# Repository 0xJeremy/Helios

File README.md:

# Helios Pi Hat Controller

### Board Layout

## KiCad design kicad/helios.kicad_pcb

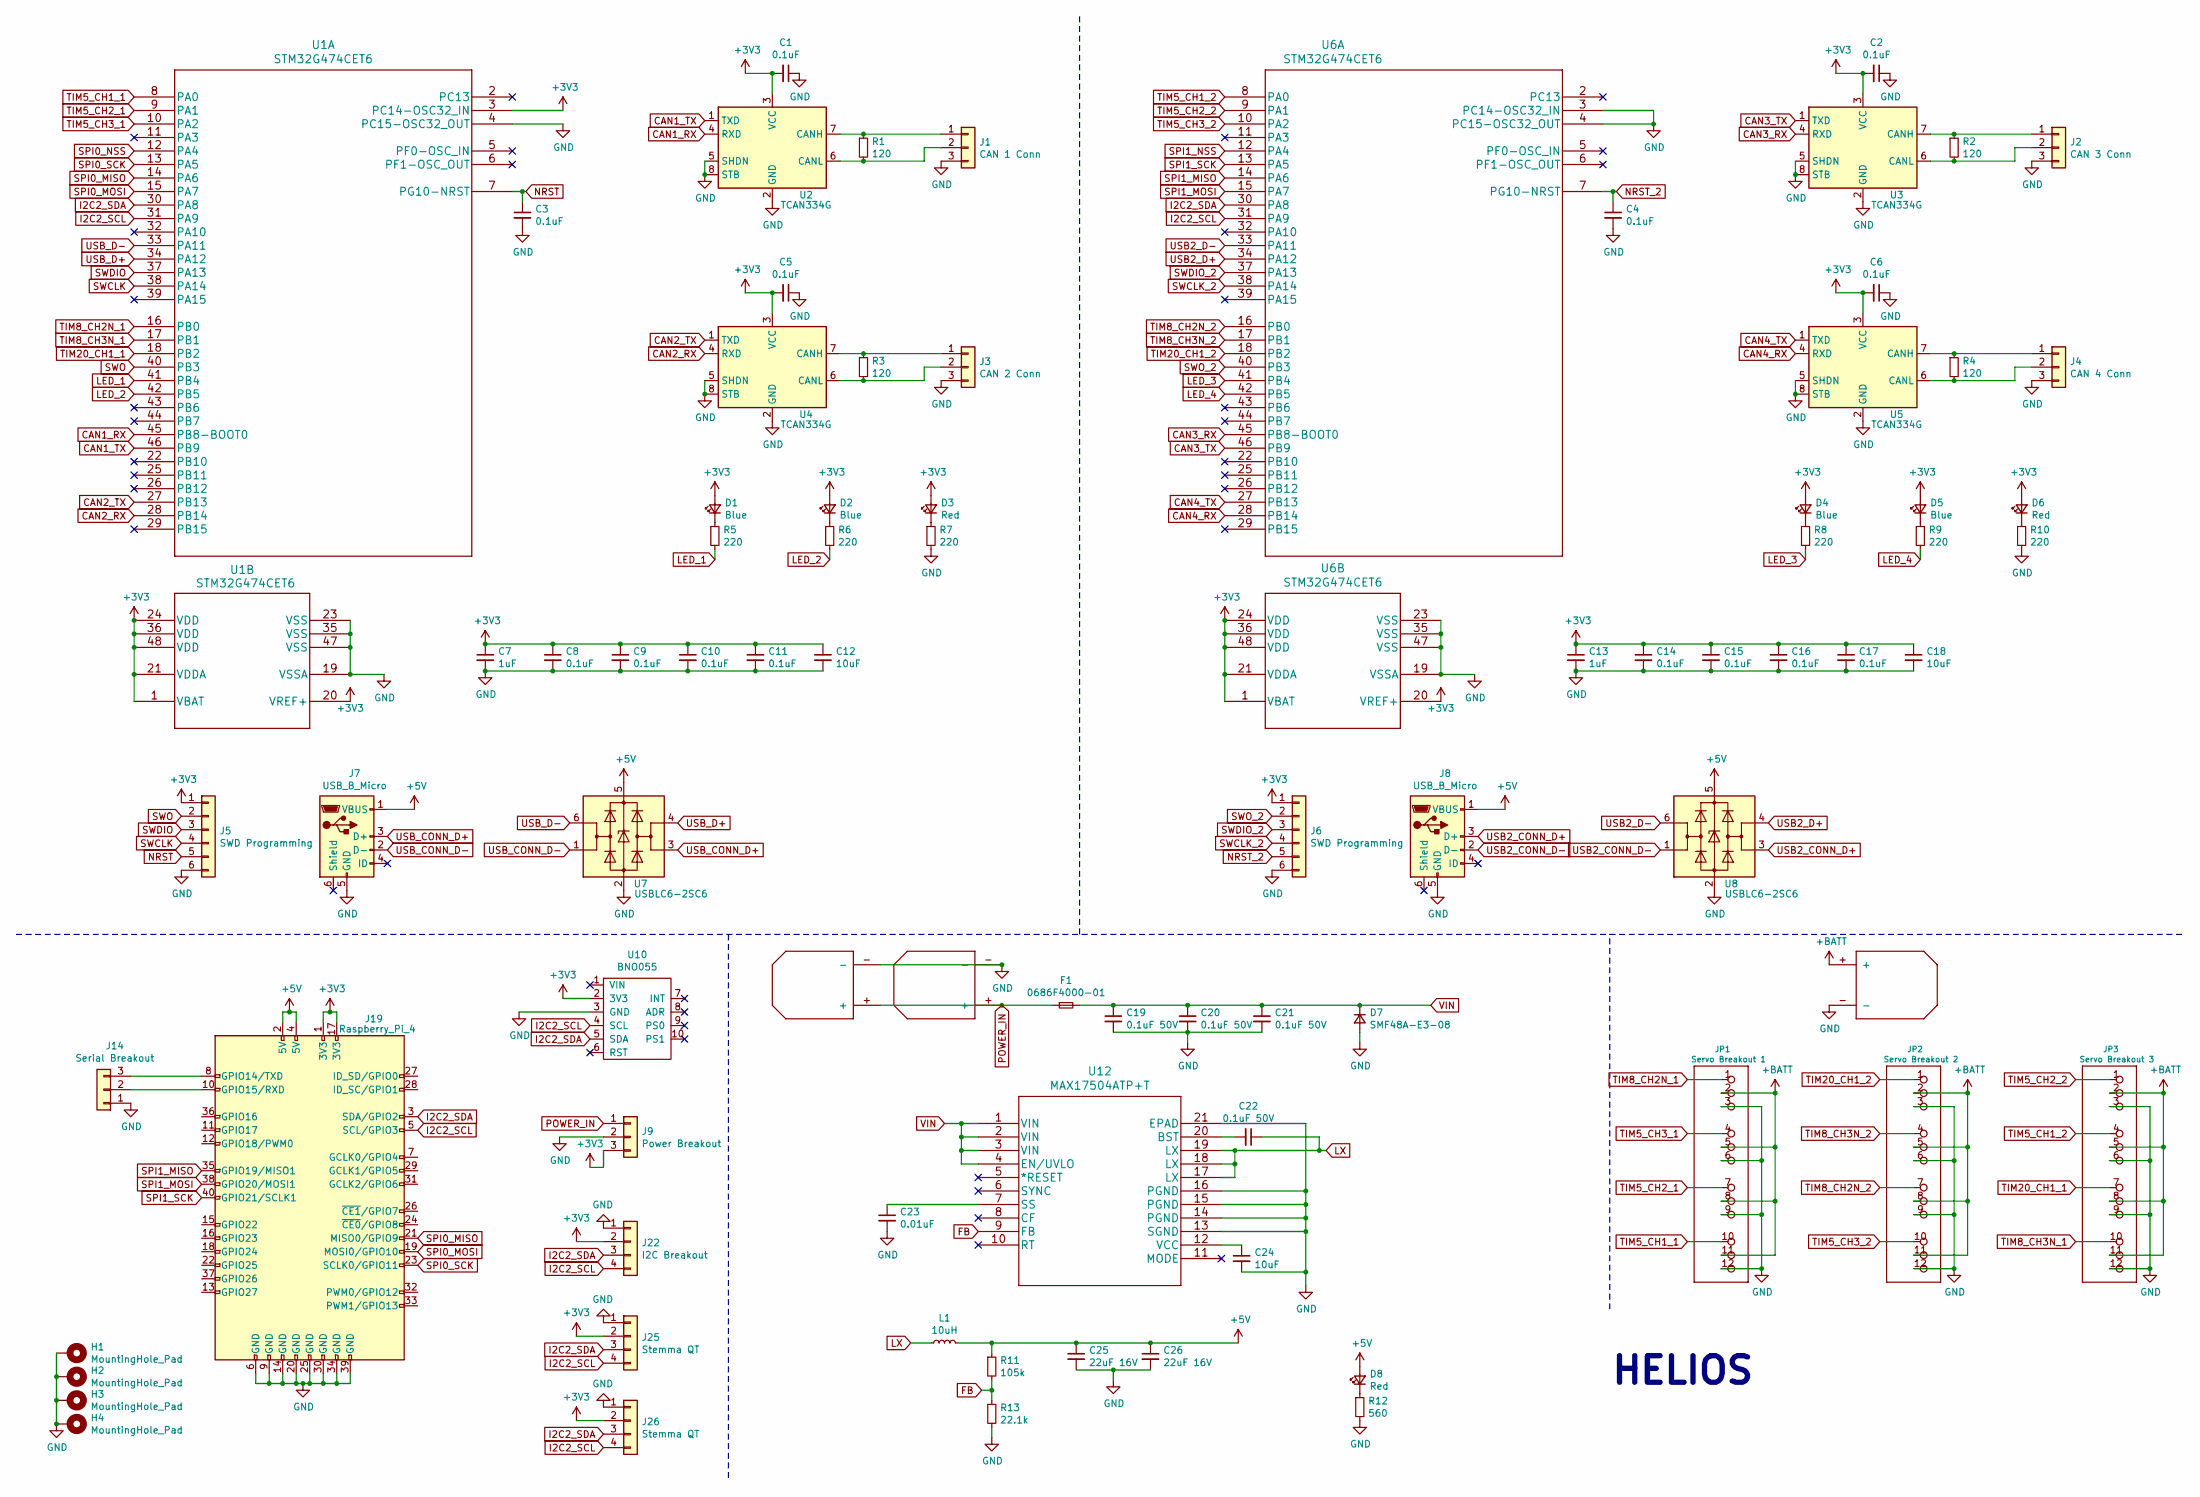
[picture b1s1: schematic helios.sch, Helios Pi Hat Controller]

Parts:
1111: XT30; XT30P
C1, C2, C3, C4, C5, C6, C8, C9, C10, C11, C14, C15, C16, C17: 0.1uF; C_0402_1005Metric
C7, C13: 1uF; C_0402_1005Metric
C12, C18: 10uF; C_0402_1005Metric
C19, C20, C21, C22: 0.1uF 50V; C_1206_3216Metric
C23: 0.01uF; C_0402_1005Metric
C24: 10uF; C_1206_3216Metric
C25, C26: 22uF 16V; C_0603_1608Metric
D1, D2, D4, D5: Blue; LED_0603_1608Metric
D3, D6, D8: Red; LED_0603_1608Metric
D7: SMF48A-E3-08; SMF
F1: 0686F4000-01; Fuse_0603_1608Metric
H1, H2, H3, H4: MountingHole_Pad; MountingHole_2.7mm_M2.5_DIN965_Pad
J1: CAN 1 Conn; JST_PH_B3B-PH-K_1x03_P2.00mm_Vertical
J2: CAN 3 Conn; JST_PH_B3B-PH-K_1x03_P2.00mm_Vertical
J3: CAN 2 Conn; JST_PH_B3B-PH-K_1x03_P2.00mm_Vertical
J4: CAN 4 Conn; JST_PH_B3B-PH-K_1x03_P2.00mm_Vertical
J5, J6: SWD Programming; JST_PH_B6B-PH-K_1x06_P2.00mm_Vertical
J7, J8: USB_B_Micro; USB_Micro-AB_Molex_47590-0001
J9: Power Breakout; Eagle_1X03
J14: Serial Breakout; Eagle_1X03
J19: Raspberry_Pi_4; Pin_Header_Straight_2x20
J22: I2C Breakout; PinHeader_1x04_P2.54mm_Vertical
J25, J26: Stemma QT; JST_SH4
JP1: Servo Breakout 1; 3X04
JP2: Servo Breakout 2; 3X04
JP3: Servo Breakout 3; 3X04
L1: 10uH; IND_YUDEN_NS10165_YDN
R1, R2, R3, R4: 120; R_0402_1005Metric
R5, R6, R7, R8, R9, R10: 220; R_0402_1005Metric
R11: 105k; R_0402_1005Metric
R12: 560; R_0402_1005Metric
R13: 22.1k; R_0402_1005Metric
U1, U6: STM32G474CET6
U2, U3, U4, U5: TCAN334G
U7, U8: USBLC6-2SC6; SOT-23-6
U9, U11: XT30; XT30P
U10: BNO055
U12: MAX17504ATP+T; MAX17504ATP&plus_T

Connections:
+3V3: C1.2, C2.2, C5.2, C6.2, C7.1, C8.1, C9.1, C10.1, C11.1, C12.1, C13.1, C14.1, C15.1, C16.1, C17.1, C18.1, D1.2 (A), D2.2 (A), D3.2 (A), D4.2 (A), D5.2 (A), D6.2 (A), J5.1, J6.1, J9.3, J19.1 (3V3), J19.17 (3V3), J22.2, J25.2, J26.2, U1.1 (VBAT), U1.3 (PC14-OSC32_IN), U1.20 (VREF+), U1.21 (VDDA), U1.24 (VDD), U1.36 (VDD), U1.48 (VDD), U2.3 (VCC), U3.3 (VCC), U4.3 (VCC), U5.3 (VCC), U6.1 (VBAT), U6.20 (VREF+), U6.21 (VDDA), U6.24 (VDD), U6.36 (VDD), U6.48 (VDD), U10.2 (3V3)
+5V: C25.1, C26.1, D8.2 (A), J7.1 (VBUS), J8.1 (VBUS), J19.2 (5V), J19.4 (5V), L1.2, R11.1, U7.5 (VBUS), U8.5 (VBUS)
+BATT: JP1.2, JP1.5, JP1.8, JP1.11, JP2.2, JP2.5, JP2.8, JP2.11, JP3.2, JP3.5, JP3.8, JP3.11, U11.+
CAN1_RX: U1.45 (PB8-BOOT0), U2.4 (RXD)
CAN1_TX: U1.46 (PB9), U2.1 (TXD)
CAN2_RX: U1.28 (PB14), U4.4 (RXD)
CAN2_TX: U1.27 (PB13), U4.1 (TXD)
CAN3_RX: U3.4 (RXD), U6.45 (PB8-BOOT0)
CAN3_TX: U3.1 (TXD), U6.46 (PB9)
CAN4_RX: U5.4 (RXD), U6.28 (PB14)
CAN4_TX: U5.1 (TXD), U6.27 (PB13)
FB: R11.2, R13.1, U12.9 (FB)
GND: 1111.-, C1.1, C2.1, C3.2, C4.2, C5.1, C6.1, C7.2, C8.2, C9.2, C10.2, C11.2, C12.2, C13.2, C14.2, C15.2, C16.2, C17.2, C18.2, C19.2, C20.2, C21.2, C23.2, C24.2, C25.2, C26.2, D7.2 (A), H1.1, H2.1, H3.1, H4.1, J1.3, J2.3, J3.3, J4.3, J5.6, J6.6, J7.5 (GND), J8.5 (GND), J9.2, J14.1, J19.6 (GND), J19.9 (GND), J19.14 (GND), J19.20 (GND), J19.25 (GND), J19.30 (GND), J19.34 (GND), J19.39 (GND), J22.1, J25.1, J26.1, JP1.3, JP1.6, JP1.9, JP1.12, JP2.3, JP2.6, JP2.9, JP2.12, JP3.3, JP3.6, JP3.9, JP3.12, R7.2, R10.2, R12.2, R13.2, U1.4 (PC15-OSC32_OUT), U1.19 (VSSA), U1.23 (VSS), U1.35 (VSS), U1.47 (VSS), U2.2 (GND), U2.5 (SHDN), U2.8 (STB), U3.2 (GND), U3.5 (SHDN), U3.8 (STB), U4.2 (GND), U4.5 (SHDN), U4.8 (STB), U5.2 (GND), U5.5 (SHDN), U5.8 (STB), U6.3 (PC14-OSC32_IN), U6.4 (PC15-OSC32_OUT), U6.19 (VSSA), U6.23 (VSS), U6.35 (VSS), U6.47 (VSS), U7.2 (GND), U8.2 (GND), U9.-, U10.3 (GND), U11.-, U12.13 (SGND), U12.14 (PGND), U12.15 (PGND), U12.16 (PGND), U12.21 (EPAD)
I2C2_SCL: J19.5 (SCL/GPIO3), J22.4, J25.4, J26.4, U1.31 (PA9), U6.31 (PA9), U10.4 (SCL)
I2C2_SDA: J19.3 (SDA/GPIO2), J22.3, J25.3, J26.3, U1.30 (PA8), U6.30 (PA8), U10.5 (SDA)
LED_1: R5.2, U1.41 (PB4)
LED_2: R6.2, U1.42 (PB5)
LED_3: R8.2, U6.41 (PB4)
LED_4: R9.2, U6.42 (PB5)
LX: C22.1, L1.1, U12.17 (LX), U12.18 (LX), U12.19 (LX)
NRST: C3.1, J5.5, U1.7 (PG10-NRST)
NRST_2: C4.1, J6.5, U6.7 (PG10-NRST)
unnamed: C22.2, U12.20 (BST)
unnamed: C23.1, U12.7 (SS)
unnamed: C24.1, U12.12 (VCC)
unnamed: D1.1 (K), R5.1
unnamed: D2.1 (K), R6.1
unnamed: D3.1 (K), R7.1
unnamed: D4.1 (K), R8.1
unnamed: D5.1 (K), R9.1
unnamed: D6.1 (K), R10.1
unnamed: D8.1 (K), R12.1
unnamed: J1.1, R1.1, U2.7 (CANH)
unnamed: J1.2, R1.2, U2.6 (CANL)
unnamed: J2.1, R2.1, U3.7 (CANH)
unnamed: J2.2, R2.2, U3.6 (CANL)
unnamed: J3.1, R3.1, U4.7 (CANH)
unnamed: J3.2, R3.2, U4.6 (CANL)
unnamed: J4.1, R4.1, U5.7 (CANH)
unnamed: J4.2, R4.2, U5.6 (CANL)
unnamed: J14.2, J19.10 (GPIO15/RXD)
unnamed: J14.3, J19.8 (GPIO14/TXD)
POWER_IN: 1111.+, F1.1, J9.1, U9.+
SPI0_MISO: J19.21 (MISO0/GPIO9), U1.14 (PA6)
SPI0_MOSI: J19.19 (MOSI0/GPIO10), U1.15 (PA7)
SPI0_NSS: U1.12 (PA4)
SPI0_SCK: J19.23 (SCLK0/GPIO11), U1.13 (PA5)
SPI1_MISO: J19.35 (GPIO19/MISO1), U6.14 (PA6)
SPI1_MOSI: J19.38 (GPIO20/MOSI1), U6.15 (PA7)
SPI1_NSS: U6.12 (PA4)
SPI1_SCK: J19.40 (GPIO21/SCLK1), U6.13 (PA5)
SWCLK: J5.4, U1.38 (PA14)
SWCLK_2: J6.4, U6.38 (PA14)
SWDIO: J5.3, U1.37 (PA13)
SWDIO_2: J6.3, U6.37 (PA13)
SWO: J5.2, U1.40 (PB3)
SWO_2: J6.2, U6.40 (PB3)
TIM5_CH1_1: JP1.10, U1.8 (PA0)
TIM5_CH1_2: JP3.4, U6.8 (PA0)
TIM5_CH2_1: JP1.7, U1.9 (PA1)
TIM5_CH2_2: JP3.1, U6.9 (PA1)
TIM5_CH3_1: JP1.4, U1.10 (PA2)
TIM5_CH3_2: JP2.10, U6.10 (PA2)
TIM8_CH2N_1: JP1.1, U1.16 (PB0)
TIM8_CH2N_2: JP2.7, U6.16 (PB0)
TIM8_CH3N_1: JP3.10, U1.17 (PB1)
TIM8_CH3N_2: JP2.4, U6.17 (PB1)
TIM20_CH1_1: JP3.7, U1.18 (PB2)
TIM20_CH1_2: JP2.1, U6.18 (PB2)
USB2_CONN_D+: J8.3 (D+), U8.3 (I/O2)
USB2_CONN_D-: J8.2 (D-), U8.1 (I/O1)
USB2_D+: U6.34 (PA12), U8.4 (I/O2)
USB2_D-: U6.33 (PA11), U8.6 (I/O1)
USB_CONN_D+: J7.3 (D+), U7.3 (I/O2)
USB_CONN_D-: J7.2 (D-), U7.1 (I/O1)
USB_D+: U1.34 (PA12), U7.4 (I/O2)
USB_D-: U1.33 (PA11), U7.6 (I/O1)
VIN: C19.1, C20.1, C21.1, D7.1 (K), F1.2, U12.1 (VIN), U12.2 (VIN), U12.3 (VIN), U12.4 (EN/UVLO)

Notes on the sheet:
HELIOS

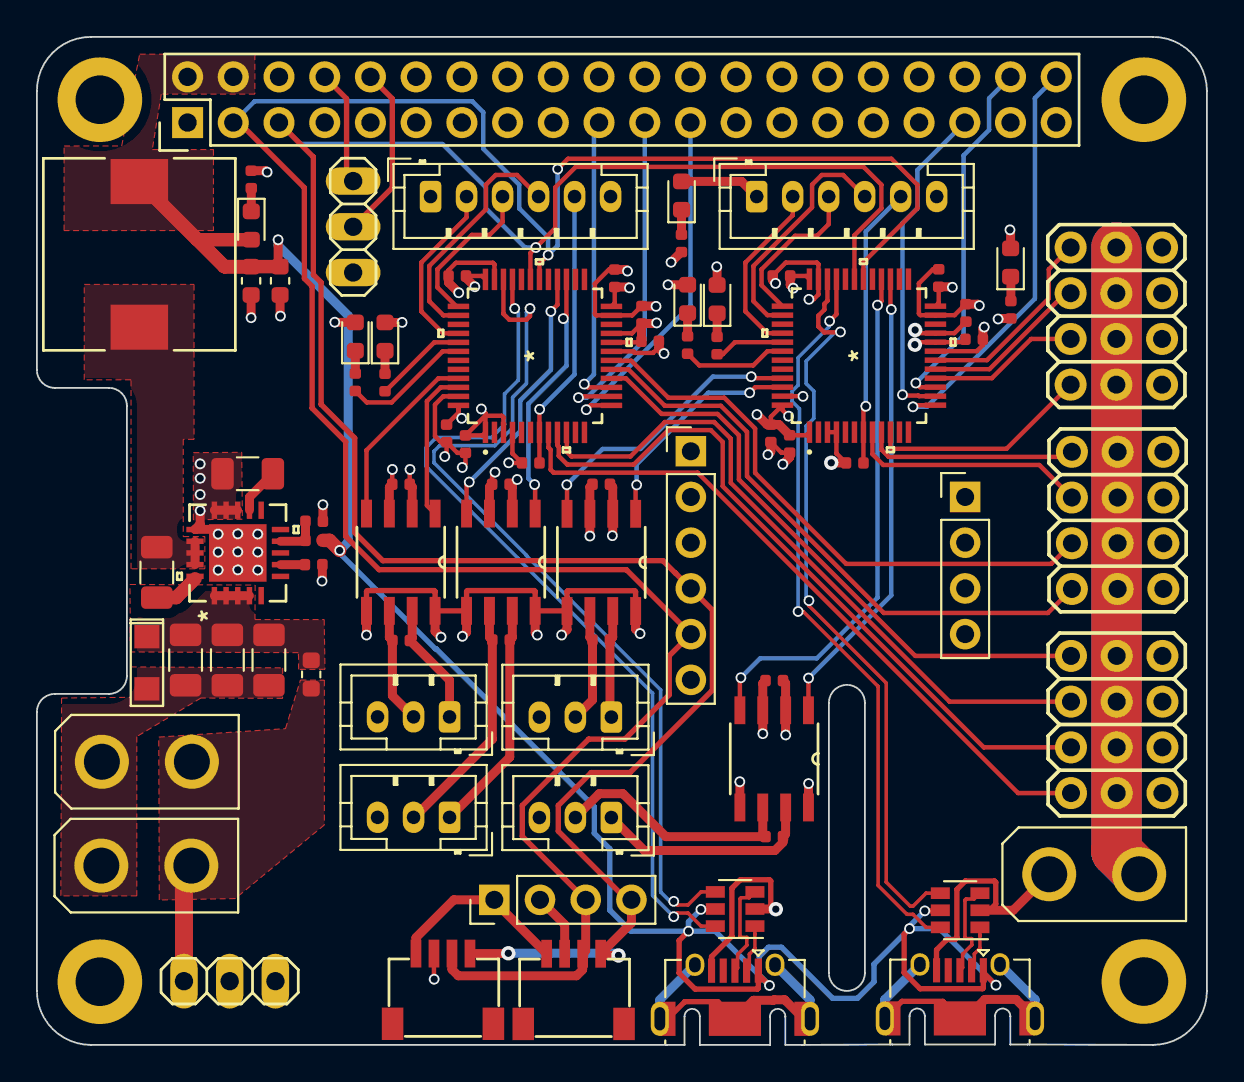
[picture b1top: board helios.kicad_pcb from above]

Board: 4 copper layers, 65.0 x 56.0 mm, 83 parts (0 on the bottom side), 76 nets.

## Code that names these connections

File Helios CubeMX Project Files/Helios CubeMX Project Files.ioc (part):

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PA6.Mode=Full_Duplex_Master
Mcu.UserName=STM32G474CETx
PA11.Mode=Device
PB13.Signal=FDCAN2_TX
PA12.Signal=USB_DP
PA4.Mode=NSS_Signal_Hard_Output
RCC.HSE_VALUE=8000000
PB3.Mode=Trace_Asynchronous_SW
PB2.Signal=TIM20_CH1
PA14.Mode=Trace_Asynchronous_SW
PA8.Signal=I2C2_SDA
PA0.Signal=S_TIM5_CH1
PB9.Signal=FDCAN1_TX
Mcu.Package=LQFP48
PA6.Signal=SPI1_MISO
PB1.Signal=TIM8_CH3N
PB12.Mode=FDCAN_Activate
PB13.Mode=FDCAN_Activate
PF1-OSC_OUT.Signal=GPIO_Output
PA5.Mode=Full_Duplex_Master
PB8-BOOT0.Mode=FDCAN_Activate
PA7.Mode=Full_Duplex_Master
PA13.Signal=SYS_JTMS-SWDIO
PA9.Mode=I2C
PB9.Mode=FDCAN_Activate
PA9.Signal=I2C2_SCL
PA1.Signal=S_TIM5_CH2
PA5.Signal=SPI1_SCK
PB0.Mode=PWM Generation2 CH2N
PB8-BOOT0.Signal=FDCAN1_RX
board=custom
PA13.Mode=Trace_Asynchronous_SW
Mcu.Name=STM32G474C(B-C-E)Tx
PA2.Signal=S_TIM5_CH3
PB3.Signal=SYS_JTDO-SWO
PA4.Signal=SPI1_NSS
RCC.SYSCLKFreq_VALUE=16000000
PA12.Mode=Device
PB2.Mode=PWM Generation1 CH1
PA11.Signal=USB_DM
PA14.Signal=SYS_JTCK-SWCLK
PB1.Mode=PWM Generation3 CH3N
PA8.Mode=I2C
PF0-OSC_IN.Signal=GPIO_Output
PB0.Signal=TIM8_CH2N
PB12.Signal=FDCAN2_RX
PA7.Signal=SPI1_MOSI

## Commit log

2021-03-11 Added README
2021-03-11 Added Helios logo
2021-03-12 Added kicad lib, began schematic, added CubeMX project files
2021-03-12 Added second MCU to schematic
2021-03-12 Added PDF schematic
2021-03-28 Majorly updated schematic, added footprints
2021-03-28 Began board layout
2021-03-30 About to start routing
2021-03-31 Finished routing
2021-03-31 Added renders
2021-04-01 Updated device addressing, added layout picture
2021-05-09 Updated README and logo
